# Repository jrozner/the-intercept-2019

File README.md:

## Case Fabrication Information (contains spoilers)

These are the top and bottom pieces for the enclosure around the PCB. They were
printed using PLA for the contest specifically to avoid issues with solvents
disolving the plastic while attempting to remove the tamper evident seals. PETG
is also a good choice but you should avoid using ABS as aceton will react badly
with it.

The hardware to screw the pieces together are M2 screws and you'll want to pick
up some matching threaded inserts to press into the plastic.

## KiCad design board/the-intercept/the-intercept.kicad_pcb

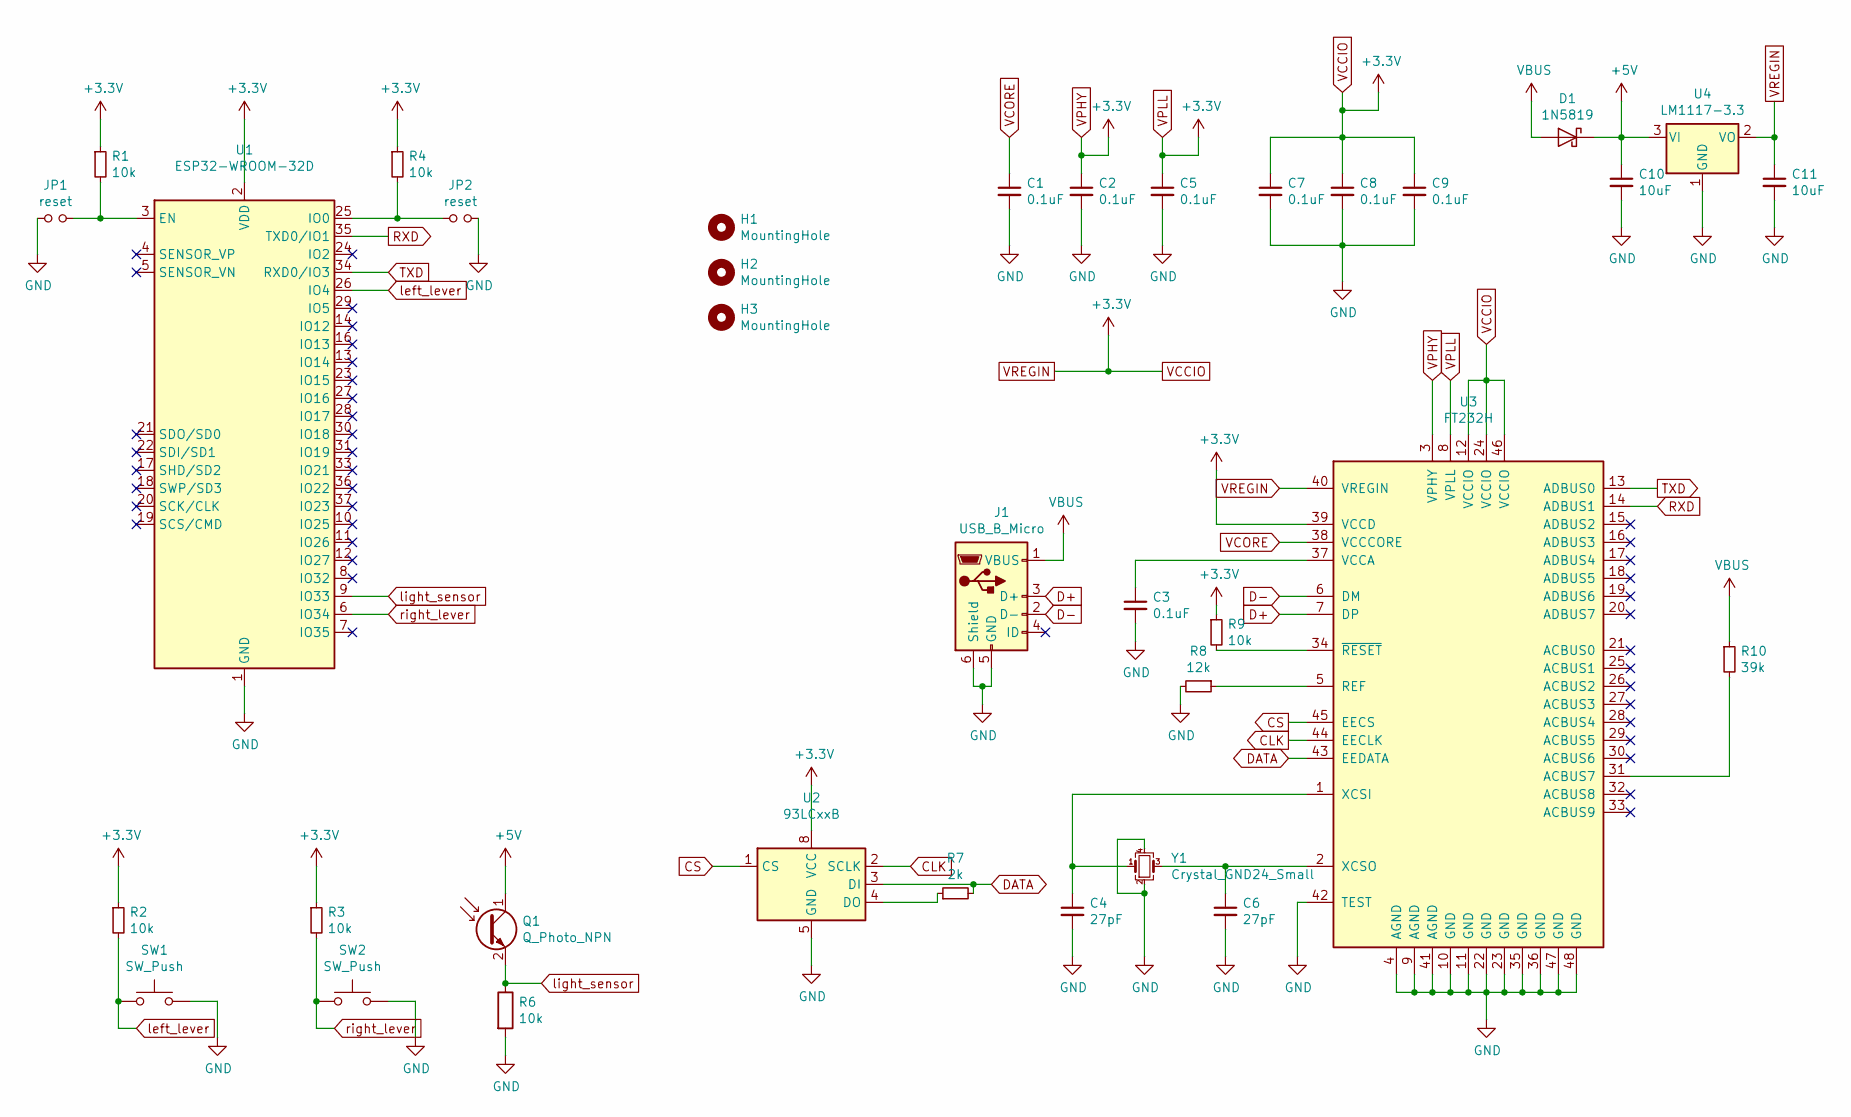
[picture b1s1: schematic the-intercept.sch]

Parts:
C1, C2, C3, C5, C7, C8, C9: 0.1uF; C_0603_1608Metric
C4, C6: 27pF; C_0603_1608Metric
C10, C11: 10uF; C_0603_1608Metric
D1: 1N5819; D_SOD-123
H1, H2, H3: MountingHole; MountingHole_2.2mm_M2
J1: USB_B_Micro; USB_Micro-B_Amphenol_10103594-0001LF_Horizontal
JP1, JP2: reset; SolderJumper-2_P1.3mm_Open_Pad1.0x1.5mm
Q1: Q_Photo_NPN; ALS-PT19
R1, R2, R3, R4, R6, R9: 10k; R_0603_1608Metric
R7: 2k; R_0603_1608Metric
R8: 12k; R_0603_1608Metric
R10: 39k; R_0603_1608Metric
SW1, SW2: SW_Push; D3SH
U1: ESP32-WROOM-32D; ESP32-WROOM-32
U2: 93LCxxB; SOIC-8_3.9x4.9mm_P1.27mm
U3: FT232H; LQFP-48_7x7mm_P0.5mm
U4: LM1117-3.3; SOT-223
Y1: Crystal_GND24_Small; Crystal_SMD_Abracon_ABM8G-4Pin_3.2x2.5mm

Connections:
+5V: C10.1, D1.1 (K), Q1.1 (C), U4.3 (VI)
CLK: U2.2 (SCLK), U3.44 (EECLK)
CS: U2.1 (CS), U3.45 (EECS)
D+: J1.3 (D+), U3.7 (DP)
D-: J1.2 (D-), U3.6 (DM)
DATA: R7.2, U2.3 (DI), U3.43 (EEDATA)
GND: C1.2, C2.2, C3.2, C4.2, C5.2, C6.2, C7.2, C8.2, C9.2, C10.2, C11.2, J1.5 (GND), J1.6 (Shield), JP1.1, JP2.2, R6.2, R8.2, SW1.2, SW2.2, U1.1 (GND), U1.15 (GND), U1.38 (GND), U2.5 (GND), U3.4 (AGND), U3.9 (AGND), U3.10 (GND), U3.11 (GND), U3.22 (GND), U3.23 (GND), U3.35 (GND), U3.36 (GND), U3.41 (AGND), U3.42 (TEST), U3.47 (GND), U3.48 (GND), U4.1 (GND), Y1.2, Y1.4
unnamed: C3.1, U3.37 (VCCA)
unnamed: C4.1, U3.1 (XCSI), Y1.1
unnamed: C6.1, U3.2 (XCSO), Y1.3
unnamed: JP1.2, R1.2, U1.3 (EN)
unnamed: JP2.1, R4.2, U1.25 (IO0)
unnamed: R7.1, U2.4 (DO)
unnamed: R8.1, U3.5 (REF)
unnamed: R9.2, U3.34 (~RESET)
unnamed: R10.2, U3.31 (ACBUS7)
RXD: U1.35 (TXD0/IO1), U3.14 (ADBUS1)
TXD: U1.34 (RXD0/IO3), U3.13 (ADBUS0)
VBUS: D1.2 (A), J1.1 (VBUS), R10.1
VCCIO: C2.1, C5.1, C7.1, C8.1, C9.1, C11.1, R1.1, R2.1, R3.1, R4.1, R9.1, U1.2 (VDD), U2.8 (VCC), U3.3 (VPHY), U3.8 (VPLL), U3.12 (VCCIO), U3.24 (VCCIO), U3.39 (VCCD), U3.40 (VREGIN), U3.46 (VCCIO), U4.2 (VO)
VCORE: C1.1, U3.38 (VCCCORE)
left_lever: R2.2, SW1.1, U1.26 (IO4)
light_sensor: Q1.2 (E), R6.1, U1.9 (IO33)
right_lever: R3.2, SW2.1, U1.6 (IO34)

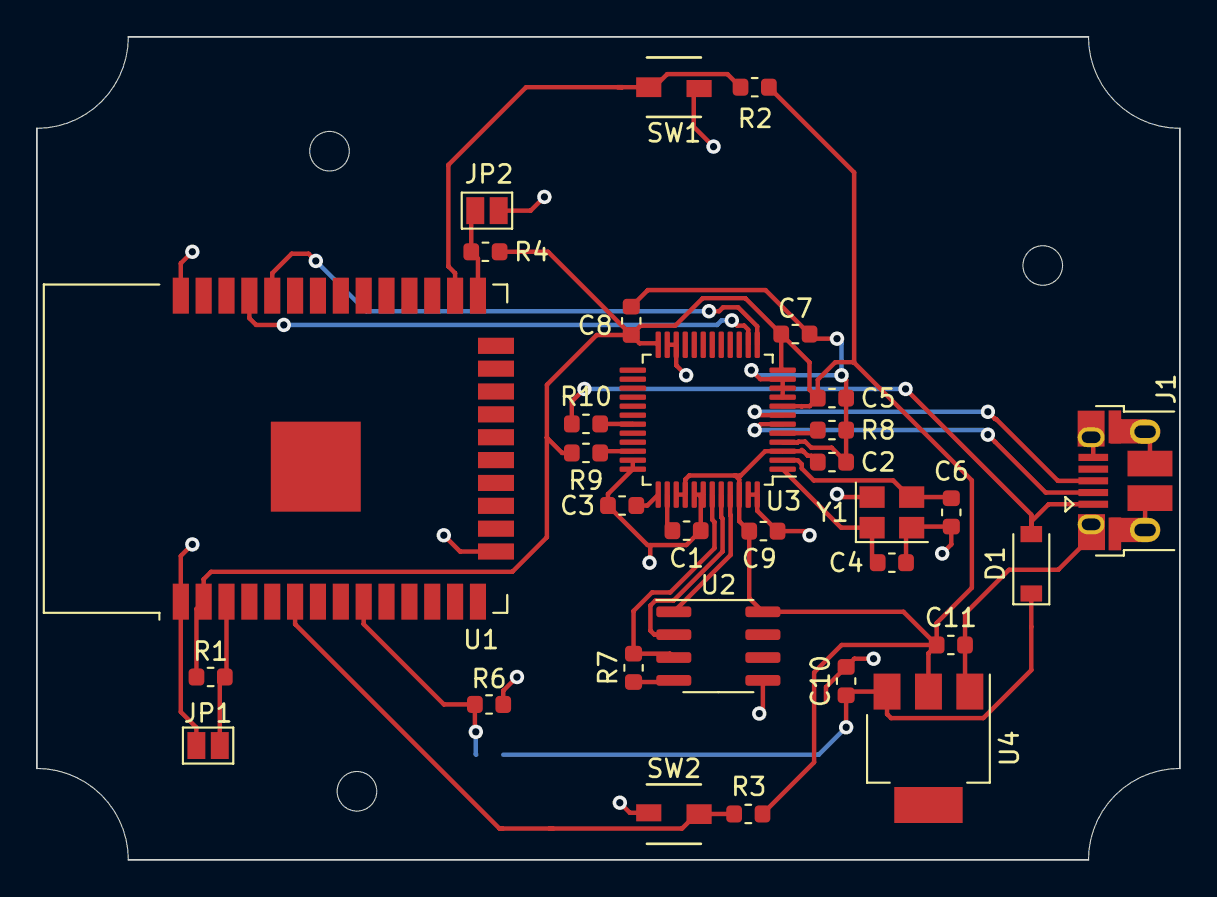
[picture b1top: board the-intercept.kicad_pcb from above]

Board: 2 copper layers, 63.5 x 45.7 mm, 35 parts (1 on the bottom side), 24 nets.

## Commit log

2019-04-29 Add board design
2019-04-29 Add .idea to gitignore
2019-05-03 Implement message sending
2019-05-03 Revision two of the board
2019-05-03 Fail if can't start the web server
2019-05-07 Updates for final board
2019-05-10 Add authorization middleware
2019-05-10 Add registration workflow
2019-05-11 Seek body back to beginning
2019-05-11 Add error handling for Seek failure
2019-05-11 Scope error messages
2019-05-12 Add client
2019-05-12 Switch to team name
2019-05-12 Update handlers for user in context
2019-05-12 Create ReadMe
    Just annoying Joe with shitty web github entries
2019-05-12 Updated comments and core code, added missing root dir files
2019-05-12 Empty component.mk required for package build, added .gitignore
2019-05-12 Added first flag, wifi checking and DEV/PROG logging control
2019-05-13 Added wifi connection check on boot and additional tamper detection code
    Currently some bullshit bug with ESP_LOGE / printf in
    sensor_handler_digi causing a stack overflow "sometimes"
2019-05-13 Fixed stack overflow issues (I think?) by increasing task stack size to 4k (prev 2k)
2019-05-13 Added tuna jokes and unregistered command (testing functionality)
2019-05-13 Unregistered function properly tagged for compilation (need to update its actual code)
2019-05-14 Added some flags and seem to have a working unregistered_cmd setup
2019-05-15 Add web client and fix bugs
2019-05-15 Remove client binary
2019-05-16 Add flag infrastructure
2019-05-16 Finish messages
    Differentiate between read and unread messages and make reading a
    message report that it has been seen
2019-05-16 Add config file to server
2019-05-16 Add serial number to signature
2019-05-16 Add error handling for unique constraint failures
2019-05-16 Remove only the user's flags on a rotate
2019-05-18 Return after running a handler
2019-05-18 Explicitly return an ok
2019-05-18 Add beginning of flagbot
2019-05-18 Add flag solving
2019-05-18 Fix compilation error
2019-05-20 Switch to flags in database
2019-05-27 Cleanup and register
2019-05-27 Add commands and help
2019-05-27 More cleanup
2019-05-27 Add debug messages
2019-05-27 Save access and secret keys
2019-05-27 Even more cleanup
2019-05-27 added tamper checks for NVS
2019-05-27 Completed admin_read function, tested vs app_main entry point
2019-05-27 Update gitignore
2019-05-27 Added CarTUNAist flag / verified
2019-05-27 Actual coders up in this JOEEEEE
2019-05-27 Admin mode added, about halfway done. includes tamper checking for admin funcs
2019-05-27 Admin login with timing vuln completed and verified
2019-05-27 prod wifi values
2019-05-27 Fixed opaque predicate for unreg cmd
2019-05-27 Corrected ESP_LOGE tamper msgs, admin_jump command added/verified
2019-05-27 Update help message
2019-05-27 Disabled wifi checking due to async bullshit, prod wifi confirmed
2019-05-27 Implement additional commands
2019-05-27 Fix a bunch of bugs and get unread working
    Auth is still broken because of a difference in signatures but
    communication is functioning when the server doesn't reject the request.
    This fixes a bunch of issues with the key storage, encoding, and
    communications
2019-05-27 Sign the body
2019-05-27 Setup production wifi and host
2019-05-27 Add message composition
2019-05-27 Add notes for database creation
2019-05-27 Add the flags
2019-05-27 Stop commands when tamper is detected
2019-05-27 Fix stupid message authentication issue
2019-05-27 Switch to prod
2019-05-27 Implement factory_reset
2019-05-27 Sodium only does 32bit keys
2019-05-27 Truncate messages in unread
2019-05-27 Let teams register when tamper detected
    It's not possible to factory reset until registered so we need to allow
    registration in order to get to a known good state
2019-06-10 Add STL files for cases
2019-06-10 Add readme for case
2019-06-10 Add BOM for purchasing
